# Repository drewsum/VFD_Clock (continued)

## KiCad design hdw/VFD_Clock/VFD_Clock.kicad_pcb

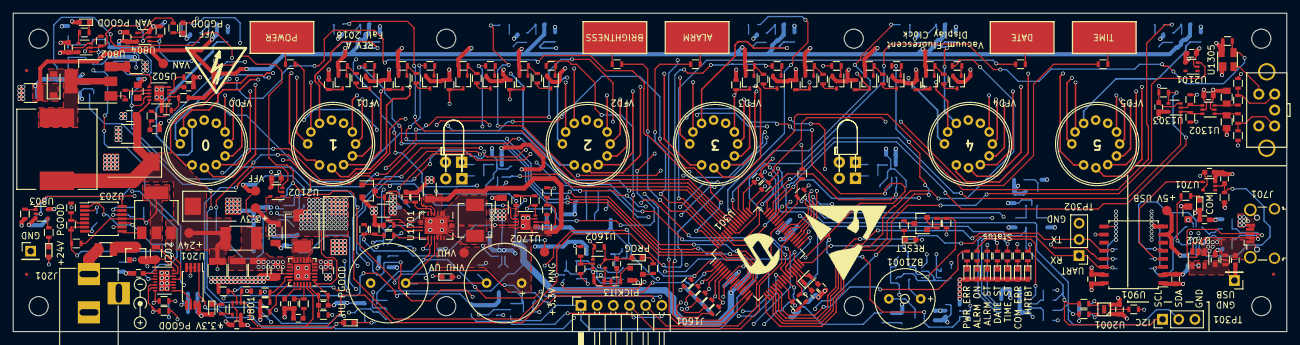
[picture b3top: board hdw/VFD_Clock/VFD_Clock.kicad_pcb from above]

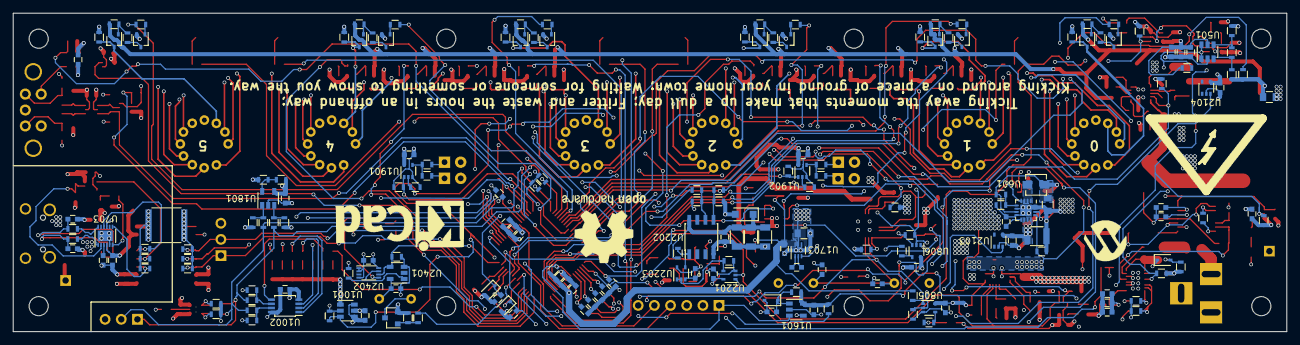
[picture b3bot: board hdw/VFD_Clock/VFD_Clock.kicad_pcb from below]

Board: 4 copper layers, 200.0 x 50.0 mm, 480 parts (186 on the bottom side), 265 nets.

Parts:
A201: 0x6F; Dummy_Empty
A301: MASTER; Dummy_Empty
A1001: 0x41; Dummy_Empty
A1801: 0x50/0x58(UID); Dummy_Empty
A2001: 0x44; Dummy_Empty
A2201: 0x6B; Dummy_Empty
BZ1001: AI-1027-TWT-3V-R
C201, C204, C302, C305, C502, C701, C703, C705, C706, C707, C801, C802, C803, C804, C805, C806, C901, C902, C1001, C1002, C1303, C1306, C1307, C1401, C1402, C1403, C1404, C1601, C1602, C1603, C1710, C1711, C1801, C1901, C1902, C2001, C2101, C2102, C2105, C2106, C2201, C2202, C2203, C2401, C2402: 0.1uF; C_0603
C202, C303, C306, C407, C503, C702, C710: 10nF; C_0603
C203, C304, C307, C504: 1nF; C_0603
C207: 2200pF; C_0603
C208, C404: 100pF; C_0603
C209, C510: 47uF; CP_Tantalum_Case-X_EIA-7343-43_Reflow
C308, C309: 9pF; C_0603
C401, C403, C405, C501, C602: 10uF; C_1210
C402: 5.1pF; C_0603
C406, C408: 1uF; C_0805
C409: 4.7pF; C_0603
C410: 100uF; C_1206
C411: 220uF; CP_Tantalum_Case-X_EIA-7343-43_Reflow
C505: 0.22uF; C_0603
C506: 6.8nF; C_0603
C507, C704: 4.7uF; C_0805
C508: 1uF; C_1210
C509, C511: 0.1uF; C_0805
C601: 150pF; C_0603
C603: 22uF; C_0805
C708, C709: 47pF; C_0603
C903: 22000pF; C_2220
C1304, C1305, C1707: 2.2uF; C_0805
C1701, C1702, C1706, C2204, C2205, C2206: 10uF; C_1206
C1703, C1704: 15F; SCCT30B156SRB
C1705: 470pF; C_0603
C1708: 1uF; C_0603
C1709: 4.7uF; C_0603
C2103, C2104, C2107, C2108: 330pF; C_0603
D501: SMD1200PL-TP‎; D_SOD-123
D702: Yellow; LED_0603
D801, D802, D803, D804, D805, D1007: Green; LED_0603
D806, D1003, D1008, D1009: Red; LED_0603
D1001, D1002: Orange; LED_0603
D1004, D1005, D1006: Blue; LED_0603
D1901, D1903: Green; LED_D3.0mm_Horizontal_O3.81mm_Z10.0mm
D1902, D1904: Green; LED_D3.0mm_Horizontal_O1.27mm_Z2.0mm
D2201: 1N5819; D_SOD-123F
F201: C1Q 2; Fuse_SMD1206_Reflow
FB401: 100; L_1812
FID2301, FID2302, FID2303: TP; Fiducial_0.5mm_Dia_1mm_Outer
J201: Power Input; BARREL_JACK
J701: USB_B_Micro; USB_Micro-B_Wuerth-629105150521_CircularHoles
J1601: Prog; PICKIT3_Header
L401: 0.82uH; L_Vishay_IHLP-2020
L501: 560uH; L_Wuerth_WE-PD-Typ-LS
L601: 2.2uH; L_Vishay_IHLP-1212
L701: 600R 0.5A; L_0603
L1701: 3.3uH; L_Vishay_IHLP-2020
MH2301, MH2302, MH2303, MH2304, MH2305, MH2306, MH2307, MH2308: 4-40 Mounting Hole; MountingHole_3mm
MK2301, MK2302, MK2303, MK2304, MK2305, MK2306, MK2307, MK2308: #4-40 Screw; Dummy_Empty
MK2309, MK2310, MK2311, MK2312, MK2313, MK2314, MK2315, MK2316: #4-40 Standoff; Dummy_Empty
Q201: Si2319CDS; SOT-23
Q202: PMT560ENEA; SOT-223
Q501: IRFL214TRPBF; SOT-223-3_TabPin2
Q1001, Q1002, Q1003, Q1701: 2N7002; SOT-23
Q1101, Q1102, Q1105, Q1106, Q1109, Q1110, Q1113, Q1114, Q1201, Q1202, Q1205, Q1206, Q1209, Q1210: PMSTA06; SOT-323_SC-70
Q1103, Q1104, Q1107, Q1108, Q1111, Q1112, Q1115, Q1116, Q1203, Q1204, Q1207, Q1208, Q1211, Q1212: BC856W; SOT-323_SC-70
R201, R203, R301, R302, R1012, R1013, R1604, R1708, R1801, R1805, R1806, R2004, R2005, R2204, R2205: 0; R_0603
R202, R204, R209, R210, R212, R303, R304, R305, R401, R405, R504, R506, R511, R601, R602, R701, R801, R802, R805, R806, R809, R810, R901, R902, R903, R904, R905, R906, R1003, R1005, R1014, R1015, R1101, R1102, R1109, R1110, R1117, R1118, R1125, R1126, R1201, R1202, R1209, R1210, R1217, R1218, R1303, R1308, R1309, R1312, R1313, R1314, R1402, R1404, R1406, R1601, R1602, R1603, R1605, R1802, R1803, R1804, R1901, R1902, R1907, R1908, R2001, R2002, R2003, R2201, R2202, R2203, R2206, R2401, R2402, R2403: 10k; R_0603
R205: 158k; R_0603
R206: 681; R_0603
R207: 3.74k; R_0603
R208, R704, R803, R804, R807, R808, R811, R812, R1004, R1006, R1007, R1008, R1009, R1010, R1011, R1016, R1018, R1310, R1311, R1408, R1903, R1904, R1905, R1906, R2101, R2102, R2103, R2104: 1k; R_0603
R211: 0.02; R_0805
R402: 49.9k; R_0603
R403: 18.2k; R_0603
R404, R1107, R1108, R1115, R1116, R1123, R1124, R1131, R1132, R1207, R1208, R1215, R1216, R1223, R1224, R1401, R1403, R1405, R1407: 100k; R_0603
R406, R1701, R1702, R1709, R1712, R1713: 1M; R_0603
R407: 412k; R_0603
R501: 196k; R_0603
R502: 237; R_0603
R503: 1.2k; R_0603
R505: 10.5k; R_0603
R507: 22k; R_0603
R508: 2; R_0603
R509: 0.51; R_1206
R510: 356k; R_0603
R603: 75k; R_0603
R604: 150k; R_0603
R702, R703: 27; R_0603
R1001, R1002, R1017: 10; R_0603
R1103, R1105, R1111, R1113, R1119, R1121, R1127, R1129, R1203, R1205, R1211, R1213, R1219, R1221: 220k; R_0603
R1104, R1106, R1112, R1114, R1120, R1122, R1128, R1130, R1204, R1206, R1212, R1214, R1220, R1222: 68k; R_0603
R1301, R1302, R1304, R1305, R1306: 220; R_0603
R1703: 124k; R_0603
R1704: 3.6k; R_0603
R1705: 2.2M; R_0603
R1706: 3.65k; R_0603
R1707: 340k; R_0603
R1710: 324k; R_0603
R1711: 276k; R_0603
SW1306: Select; ACZ11BR4E-15FA1-20C
TP201, TP702: TP; Pin_Header_Straight_1x01_Pitch2.54mm
TP203, TP401, TP501, TP601, TP701, TP1701, TP1702: TP; Measurement_Point_Round-SMD-Pad_Small
TP301: I2C; Pin_Header_Straight_1x03_Pitch2.54mm
TP302: USB_UART; Pin_Header_Straight_1x03_Pitch2.54mm
TP1301, TP1303: Date; SolderWirePad_single_SMD_5x10mm
TP1302: Time; SolderWirePad_single_SMD_5x10mm
TP1304: Alarm; SolderWirePad_single_SMD_5x10mm
TP1305: Brightness; SolderWirePad_single_SMD_5x10mm
U201: CDCS503; TSSOP-8_4.4x3mm_Pitch0.65mm
U202: LTC2946DE; DFN-16-1EP_3x4mm_Pitch0.45mm
U203: TPS2411PWR; TSSOP-14_4.4x5mm_Pitch0.65mm
U301: PIC18LF67K40-I_PT; TQFP-64_10x10mm_Pitch0.5mm
U401: LT8643S; QFN-24-1EP_4x4mm_Pitch0.5mm
U501: LT6700-1-S6; SOT-23-6
U502: LT3757; DFN-10-1EP_3x3mm_Pitch0.5mm
U601: TPS62150; QFN-16-1EP_3x3mm_Pitch0.5mm
U701: 74LVC1G17; SOT-353_SC-70-5
U702: TPD3S014DBVR; SOT-23-6
U703: FT234XD; DFN-12-1EP_3x3mm_Pitch0.45mm
U801, U802, U803, U804, U805, U1901, U1902, U2203: 74LVC1G38; SOT-353_SC-70-5
U806: 74LVC1G240; SOT-353_SC-70-5
U901: ISO7331C; SOIC-16W_7.5x10.3mm_Pitch1.27mm
U1001: TPS22929D; SOT-23-6
U1002: PCA9536DP; TSSOP-8_3x3mm_Pitch0.65mm
U1302: 74LVC2G14; SOT-363_SC-70-6
U1303: 74LVC1G79; SOT-353_SC-70-5
U1305: MAX6816; SOT-143
U1601: TL331; SOT-23-5
U1602: 74LVC1G86; SOT-353_SC-70-5
U1701: LTC3128-UFD; QFN-20-1EP_4x5mm_Pitch0.5mm
U1702: LTC4419DD; DFN-10-1EP_3x3mm_Pitch0.5mm
U1703: LTC3221; DFN-6-1EP_2x2mm_Pitch0.5mm
U1801: AT24CS01-STUM; SOT-23-5
U2001: OPT3001; USON-6_1EP_2mmx2mm_p0.65mm
U2101, U2102, U2103, U2104: MCP9700AT-HLT; SOT-353_SC-70-5
U2201: 74LVC1G08; SOT-353_SC-70-5
U2202: DS1683; SOIC-8_3.9x4.9mm_Pitch1.27mm
U2401: STWD100YNWWY3F; SOT-23-5
U2402: 74LVC2G74; VSSOP-8_2.3x2mm_Pitch0.5mm
VFD0, VFD1, VFD2, VFD3, VFD4, VFD5: IV-6
Y301: 32.768kHz; Crystal_SMD_2012-2pin_2.0x1.2mm
Z201: MMSZ5240BS; D_SOD-323
Z1402, Z1403: BZT52C3V3S; D_SOD-323
Z1601: BZT52C5V6S; D_SOD-323

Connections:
+3.3V_MNG: C302.1, C303.1, C304.1, C305.1, C306.1, C307.1, C1709.1, R305.2, R1701.2, R1712.2, R1713.2, TP1702.1, U301.10, U301.38, U1703.6
+3V3: BZ1001.1, C201.1, C202.1, C203.1, C409.1, C410.1, C411.1, C502.1, C503.1, C504.1, C602.1, C801.1, C802.1, C803.1, C804.1, C805.1, C806.1, C901.1, C1001.1, C1002.1, C1303.1, C1306.1, C1307.1, C1603.1, C1701.1, C1801.1, C1901.1, C1902.1, C2001.1, C2101.1, C2102.1, C2105.1, C2106.1, C2201.1, C2203.1, C2401.1, C2402.1, D801.2, D802.2, D803.2, D804.2, D805.2, D806.2, D1001.2, D1009.2, D1901.2, D1902.2, D1903.2, D1904.2, D2201.2, J1601.2, L401.2, R204.2, R209.2, R210.2, R303.2, R304.2, R401.2, R406.1, R504.2, R602.1, R1014.2, R1015.2, R1303.1, R1308.1, R1309.1, R1401.2, R1602.2, R1603.2, R1702.2, R1801.2, R1803.2, R1804.2, R2002.1, R2003.1, R2202.2, R2203.2, R2402.2, TP401.1, U201.7, U201.8, U401.1, U501.5, U601.10, U601.11, U601.12, U801.5, U802.5, U803.5, U804.5, U805.5, U806.5, U901.10, U901.16, U1001.4, U1001.6, U1002.8, U1302.5, U1303.5, U1305.4, U1602.5, U1701.7, U1801.4, U1901.5, U1902.5, U2001.1, U2101.4, U2102.4, U2103.4, U2104.4, U2201.5, U2203.5, U2401.5, U2402.8
+5V_USB: C701.1, C703.1, C704.1, C705.1, C902.1, D702.2, R701.1, TP701.1, U701.5, U702.4, U703.4, U703.9, U901.1, U901.7
+24V: C209.1, C401.1, C501.1, C510.1, C511.1, C1602.1, FB401.1, L501.1, Q202.3, R1405.2, R1601.2, TP203.1, U203.1, U203.10, U502.10, U1601.5
/USB/UART Converter/BRIDGE_USB+: R702.1, U703.12
/USB/UART Converter/BRIDGE_USB-: R703.2, U703.1
/USB/UART Converter/CONN_USB+: C708.1, J701.3, R702.2, U702.5
/USB/UART Converter/CONN_USB-: C709.1, J701.2, R703.1, U702.6
ACCUM: R212.2, U202.4, U301.36
Alarm_mTouch: R1305.2, U301.62
Ambient_Temp: C2103.1, R2101.1, U301.3
Anode_A: Q1103.3, R1107.1, VFD0.2, VFD1.2, VFD2.2, VFD3.2, VFD4.2, VFD5.2
Anode_B: Q1107.3, R1115.1, VFD0.1, VFD1.1, VFD2.1, VFD3.1, VFD4.1, VFD5.1
Anode_C: Q1111.3, R1123.1, VFD0.10, VFD1.10, VFD2.10, VFD3.10, VFD4.10, VFD5.10
Anode_D: Q1115.3, R1131.1, VFD0.6, VFD1.6, VFD2.6, VFD3.6, VFD4.6, VFD5.6
Anode_DP: Q1116.3, R1132.1, VFD0.11, VFD1.11, VFD2.11, VFD3.11, VFD4.11, VFD5.11
Anode_E: Q1104.3, R1108.1, VFD0.5, VFD1.5, VFD2.5, VFD3.5, VFD4.5, VFD5.5
Anode_F: Q1108.3, R1116.1, VFD0.4, VFD1.4, VFD2.4, VFD3.4, VFD4.4, VFD5.4
Anode_G: Q1112.3, R1124.1, VFD0.3, VFD1.3, VFD2.3, VFD3.3, VFD4.3, VFD5.3
Brightness_mTouch: R1306.2, U301.63
Buzzer: R1002.2, U301.25
Colon_1: R1901.1, U301.57, U1901.1
Colon_2: R1908.1, U301.56, U1902.1
DIM_PWM: R801.1, R802.1, R805.1, R806.1, R809.1, R810.1, R1003.1, R1902.1, R1907.1, U301.8, U801.2, U802.2, U803.2, U804.2, U805.2, U806.2, U1001.3, U1901.2, U1902.2
Date_mTouch: R1301.2, U301.61
Display_mTouch: R1304.2, U301.64
Encoder_DIR: R1314.1, U301.47, U1303.4
Encoder_STEP: R1312.1, U301.48, U1302.6, U1303.1
GND: C201.2, C202.2, C203.2, C204.2, C209.2, C302.2, C303.2, C304.2, C305.2, C306.2, C307.2, C308.2, C309.2, C401.2, C402.2, C403.2, C404.2, C405.2, C406.2, C407.2, C408.2, C410.2, C411.2, C501.2, C502.2, C503.2, C504.2, C505.2, C506.2, C507.2, C508.2, C509.2, C510.2, C511.2, C601.2, C602.2, C603.2, C801.2, C802.2, C803.2, C804.2, C805.2, C806.2, C901.2, C903.2, C1001.2, C1002.2, C1303.2, C1304.2, C1305.2, C1306.2, C1307.2, C1401.2, C1402.2, C1403.2, C1404.2, C1601.2, C1602.2, C1603.2, C1701.2, C1702.2, C1704.2, C1705.2, C1706.2, C1707.2, C1709.2, C1711.2, C1801.2, C1901.2, C1902.2, C2001.2, C2101.2, C2102.2, C2103.2, C2104.2, C2105.2, C2106.2, C2107.2, C2108.2, C2201.2, C2202.2, C2203.2, C2204.2, C2205.2, C2206.2, C2401.2, C2402.2, J201.2, J201.3, J1601.3, Q1001.2, Q1002.2, Q1003.2, Q1101.2, Q1102.2, Q1105.2, Q1106.2, Q1109.2, Q1110.2, Q1113.2, Q1114.2, Q1201.2, Q1202.2, Q1205.2, Q1206.2, Q1209.2, Q1210.2, Q1701.2, R202.1, R207.1, R208.1, R212.1, R403.2, R405.2, R407.2, R503.2, R505.2, R506.2, R509.2, R511.2, R601.2, R604.2, R801.2, R802.2, R805.2, R806.2, R809.2, R810.2, R901.1, R902.1, R903.1, R1003.2, R1005.1, R1107.2, R1108.2, R1115.2, R1116.2, R1123.2, R1124.2, R1131.2, R1132.2, R1207.2, R1208.2, R1215.2, R1216.2, R1223.2, R1224.2, R1312.2, R1313.2, R1314.2, R1402.1, R1404.1, R1406.1, R1408.1, R1604.1, R1605.1, R1703.1, R1704.1, R1707.1, R1711.1, R1802.1, R1901.2, R1902.2, R1907.2, R1908.2, R2001.2, R2201.1, R2401.1, R2403.1, SW1306.C, SW1306.S1, TP201.1, TP301.3, TP302.3, U201.2, U201.3, U201.4, U201.5, U202.11, U202.12, U202.14, U202.17, U203.7, U203.9, U301.9, U301.41, U401.3, U401.16, U401.25, U501.2, U502.5, U502.11, U601.6, U601.8, U601.15, U601.16, U601.17, U801.3, U802.3, U803.3, U804.3, U805.3, U806.3, U901.9, U901.15, U1001.2, U1001.5, U1002.4, U1302.2, U1303.3, U1305.1, U1601.2, U1602.3, U1701.21, U1702.4, U1702.11, U1703.4, U1703.7, U1801.2, U1901.3, U1902.3, U2001.3, U2101.2, U2102.2, U2103.2, U2104.2, U2201.3, U2202.4, U2203.3, U2401.3, U2402.1, U2402.2, U2402.4, VFD0.7, VFD1.7, VFD2.7, VFD3.7, VFD4.7, VFD5.7, Z1402.2, Z1403.2, Z1601.2
GND_USB: C701.2, C702.2, C703.2, C704.2, C705.2, C706.2, C707.2, C708.2, C709.2, C710.2, C902.2, C903.1, J701.5, R904.1, R905.1, R906.1, TP702.1, U701.3, U702.2, U703.5, U703.13, U901.2, U901.8
Grid_0: Q1203.3, R1207.1, VFD0.9
Grid_1: Q1207.3, R1215.1, VFD1.9
Grid_2: Q1211.3, R1223.1, VFD2.9
Grid_3: Q1204.3, R1208.1, VFD3.9
Grid_4: Q1208.3, R1216.1, VFD4.9
Grid_5: Q1212.3, R1224.1, VFD5.9
HOLDUP_ADC: R1708.1, U301.34
HOLDUP_PGOOD: R1701.1, U301.33, U805.1, U1701.12
ICSPCLK: J1601.5, U301.42
ICSPDAT: J1601.4, U301.37
ICSP_DETECT: R1001.2, R1605.2, U1602.4
IIC_SCL: R201.1, R301.1, R1013.1, R1805.1, R2005.2, R2204.1, TP301.1
IIC_SDA: R203.1, R302.1, R1012.1, R1806.1, R2004.1, R2205.1, TP301.2
MID: C1703.2, C1704.1, C1710.2, C1711.1, U1701.13
unnamed: BZ1001.2, Q1002.3
unnamed: C204.1, U202.2
unnamed: C207.1, C208.1, Q202.2, Q202.4, R205.2, R211.2, U202.15, U203.11
unnamed: C207.2, U203.13
unnamed: C208.2, U203.12
unnamed: C402.1, R402.1, U401.22
unnamed: C403.1, C405.1, C406.1, C408.1, FB401.2, R404.1, U401.5, U401.6, U401.13, U401.14
unnamed: C404.1, R402.2
unnamed: C407.1, U401.21
unnamed: C409.2, R406.2, R407.1, U401.24
unnamed: C505.1, U502.3
unnamed: C506.1, R507.2
unnamed: C507.1, U502.8
unnamed: C601.1, U601.9
unnamed: C702.1, R701.2, U701.2, U703.2
unnamed: C706.1, U703.3
unnamed: C707.1, L701.2, U702.1, U702.3
unnamed: C710.1, J701.1, L701.1
unnamed: C1304.1, R1310.2, U1302.1
unnamed: C1305.1, R1311.2, U1302.3
unnamed: C1601.1, R1601.1, U1601.1, Z1601.1
unnamed: C1702.1, R1709.2, U1701.2, U1701.3, U1702.1
unnamed: C1705.1, R1704.2, U1701.5
unnamed: C1706.1, C1707.1, U1702.8, U1703.3, U1703.5
unnamed: C1708.1, U1703.1
unnamed: C1708.2, U1703.2
unnamed: C2202.1, C2204.1, C2205.1, C2206.1, D2201.1, R2206.2, U2202.8
unnamed: D501.2, L501.2, Q501.2
unnamed: D702.1, R704.1
unnamed: D801.1, R803.1
unnamed: D802.1, R804.1
unnamed: D803.1, R807.1
unnamed: D804.1, R808.1
unnamed: D805.1, R811.1
unnamed: D806.1, R812.1
unnamed: D1001.1, R1004.2
unnamed: D1002.1, R1006.2
unnamed: D1003.1, R1007.2
unnamed: D1004.1, R1008.2
unnamed: D1005.1, R1009.2
unnamed: D1006.1, R1010.2
unnamed: D1007.1, R1011.2
unnamed: D1008.1, R1016.2
unnamed: D1009.1, R1018.2
unnamed: D1901.1, R1903.1
unnamed: D1902.1, R1904.1
unnamed: D1903.1, R1905.1
unnamed: D1904.1, R1906.1
unnamed: F201.1, Q201.3
unnamed: F201.2, J201.1
unnamed: L401.1, U401.8, U401.9, U401.10, U401.11, U401.12
unnamed: L601.1, U601.1, U601.2, U601.3
unnamed: L1701.1, U1701.1, U1701.19
unnamed: L1701.2, U1701.17, U1701.18
unnamed: Q201.1, R202.2, Z201.2
unnamed: Q201.2, R211.1, U202.1, U202.16, Z201.1
unnamed: Q202.1, U203.8
unnamed: Q501.1, R508.1
unnamed: Q501.3, R509.1, U502.6
unnamed: Q1001.1, R1001.1
unnamed: Q1001.3, R1004.1
unnamed: Q1002.1, R1002.1, R1005.2
unnamed: Q1003.1, R1017.1
unnamed: Q1003.3, R1018.1
unnamed: Q1101.1, R1101.2
unnamed: Q1101.3, R1104.2
unnamed: Q1102.1, R1102.2
unnamed: Q1102.3, R1106.2
unnamed: Q1103.1, R1103.2, R1104.1
unnamed: Q1104.1, R1105.2, R1106.1
unnamed: Q1105.1, R1109.2
unnamed: Q1105.3, R1112.2
unnamed: Q1106.1, R1110.2
unnamed: Q1106.3, R1114.2
unnamed: Q1107.1, R1111.2, R1112.1
unnamed: Q1108.1, R1113.2, R1114.1
unnamed: Q1109.1, R1117.2
unnamed: Q1109.3, R1120.2
unnamed: Q1110.1, R1118.2
unnamed: Q1110.3, R1122.2
unnamed: Q1111.1, R1119.2, R1120.1
unnamed: Q1112.1, R1121.2, R1122.1
unnamed: Q1113.1, R1125.2
unnamed: Q1113.3, R1128.2
unnamed: Q1114.1, R1126.2
unnamed: Q1114.3, R1130.2
unnamed: Q1115.1, R1127.2, R1128.1
unnamed: Q1116.1, R1129.2, R1130.1
unnamed: Q1201.1, R1201.2
unnamed: Q1201.3, R1204.2
unnamed: Q1202.1, R1202.2
unnamed: Q1202.3, R1206.2
unnamed: Q1203.1, R1203.2, R1204.1
unnamed: Q1204.1, R1205.2, R1206.1
unnamed: Q1205.1, R1209.2
unnamed: Q1205.3, R1212.2
unnamed: Q1206.1, R1210.2
unnamed: Q1206.3, R1214.2
unnamed: Q1207.1, R1211.2, R1212.1
unnamed: Q1208.1, R1213.2, R1214.1
unnamed: Q1209.1, R1217.2
unnamed: Q1209.3, R1220.2
unnamed: Q1210.1, R1218.2
unnamed: Q1210.3, R1222.2
unnamed: Q1211.1, R1219.2, R1220.1
unnamed: Q1212.1, R1221.2, R1222.1
unnamed: Q1701.1, U1702.7
unnamed: Q1701.3, R1702.1, U1701.4, U1701.9
unnamed: R201.2, R210.1, U202.8
unnamed: R203.2, R204.1, U202.6, U202.7
unnamed: R205.1, R206.2, U202.13, U203.6
unnamed: R206.1, R207.2, U203.5
unnamed: R208.2, U203.2
unnamed: R301.2, R304.1, U301.50
unnamed: R302.2, R303.1, U301.49
unnamed: R403.1, U401.18
unnamed: R404.2, R405.1, U401.17
unnamed: R501.2, R502.1, U501.3
unnamed: R502.2, R503.1, U501.4
unnamed: R505.1, U502.4
unnamed: R507.1, U502.1
unnamed: R508.2, U502.7
unnamed: R510.2, R511.1, U502.2
unnamed: R603.2, R604.1, U601.5
unnamed: R803.2, U801.4
unnamed: R804.2, U802.4
unnamed: R807.2, U803.4
unnamed: R808.2, U804.4
unnamed: R811.2, U805.4
unnamed: R812.2, U806.4
unnamed: R1012.2, R1015.1, U1002.7
unnamed: R1013.2, R1014.1, U1002.6
unnamed: R1301.1, TP1301.1
unnamed: R1302.1, TP1302.1
unnamed: R1304.1, TP1303.1
unnamed: R1305.1, TP1304.1
unnamed: R1306.1, TP1305.1
unnamed: R1308.2, R1310.1, SW1306.A
unnamed: R1309.2, R1311.1, SW1306.B
unnamed: R1313.1, U1302.4, U1303.2
unnamed: R1602.1, U1601.4, U1602.1
unnamed: R1603.1, R1604.2, U1602.2
unnamed: R1703.2, U1701.10
unnamed: R1705.1, R1706.2, U1701.11
unnamed: R1706.1, R1707.2, R1708.2, U1702.9
unnamed: R1709.1, R1710.2, U1702.3
unnamed: R1710.1, R1711.2, U1702.2
unnamed: R1801.1, R1802.2, U1801.5
unnamed: R1803.1, R1805.2, U1801.3
unnamed: R1804.1, R1806.2, U1801.1
unnamed: R1903.2, R1904.2, U1901.4
unnamed: R1905.2, R1906.2, U1902.4
unnamed: R2001.1, U2001.2
unnamed: R2002.2, R2004.2, U2001.6
unnamed: R2003.2, R2005.1, U2001.4
unnamed: R2101.2, U2101.3
unnamed: R2102.2, U2102.3
unnamed: R2103.2, U2103.3
unnamed: R2104.2, U2104.3
unnamed: R2201.2, U2201.4, U2203.1, U2203.2
unnamed: R2202.1, R2204.2, U2202.5
unnamed: R2203.1, R2205.2, U2202.6
unnamed: R2206.1, U2202.1, U2203.4
unnamed: R2402.1, U2401.1, U2402.7
unnamed: SW1306.S2, U1305.2
unnamed: U201.6, U202.9
POS3P3_ADC: C1401.1, R1401.1, R1402.2, U301.1
POS3P3_PGOOD: R401.1, U301.2, U401.23, U801.1
POS3P3_TEMP: C2107.1, R2103.1, U301.6
POS24_ADC: C1403.1, R1405.1, R1406.2, U301.23, Z1402.1
POS24_PGOOD: R209.1, U203.14, U301.24, U803.1
REF_CLK: U201.1, U301.31
Reset_Detect: R1017.2, R2403.2, U2402.5
Time_mTouch: R1302.2, U301.60
USB_DTR: R902.2, U301.46, U901.13
USB_DTR_ISO: R905.2, U701.4, U901.4
USB_UART_RX: R903.2, TP302.1, U301.20, U901.14
USB_UART_RX_ISO: R904.2, U703.7, U901.3
USB_UART_TX: R901.2, TP302.2, U301.19, U901.12
USB_UART_TX_ISO: R906.2, U703.10, U901.5
VAN: C508.1, C509.1, D501.1, Q1103.2, Q1104.2, Q1107.2, Q1108.2, Q1111.2, Q1112.2, Q1115.2, Q1116.2, Q1203.2, Q1204.2, Q1207.2, Q1208.2, Q1211.2, Q1212.2, R501.1, R510.1, R1103.1, R1105.1, R1111.1, R1113.1, R1119.1, R1121.1, R1127.1, R1129.1, R1203.1, R1205.1, R1211.1, R1213.1, R1219.1, R1221.1, R1407.2, TP501.1
VAN_ADC: C1404.1, R1407.1, R1408.2, U301.28, Z1403.1
VAN_PGOOD: R504.1, U301.27, U501.1, U501.6, U802.1, U2201.1
VAN_RUN: R506.1, U301.26, U502.9
VAN_Temp: C2108.1, R2104.1, U301.5
VD: D1002.2, D1003.2, D1004.2, D1005.2, D1006.2, D1007.2, D1008.2, U1001.1
VFF: C603.1, L601.2, R603.1, R1403.2, TP601.1, U601.7, U601.14, VFD0.8, VFD1.8, VFD2.8, VFD3.8, VFD4.8, VFD5.8
VFF_ADC: C1402.1, R1403.1, R1404.2, U301.43
VFF_PGOOD: R602.2, U301.44, U601.4, U804.1, U2201.2
VFF_RUN: R601.1, U301.45, U601.13
VFF_Temp: C2104.1, R2102.1, U301.4
VHU: C1703.1, C1710.1, R1705.2, TP1701.1, U1701.14, U1701.15, U1701.16, U1702.10
Watchdog_Poke: R2401.2, U301.32, U2401.4, U2402.6
drive_Anode_A: R1101.1, U301.18
drive_Anode_B: R1109.1, U301.17
drive_Anode_C: R1117.1, U301.16
drive_Anode_D: R1125.1, U301.15
drive_Anode_DP: R1126.1, U301.11
drive_Anode_E: R1102.1, U301.14
drive_Anode_F: R1110.1, U301.13
drive_Anode_G: R1118.1, U301.12
drive_Grid_0: R1201.1, U301.58
drive_Grid_1: R1209.1, U301.55
drive_Grid_2: R1217.1, U301.54
drive_Grid_3: R1202.1, U301.53
drive_Grid_4: R1210.1, U301.52
drive_Grid_5: R1218.1, U301.51
uC_SOSC+: C308.1, U301.29, Y301.1
uC_SOSC-: C309.1, U301.30, Y301.2
~Encoder_PB: R1303.2, U301.59, U1305.3
~HOLDUP_UV: R1713.1, U806.1, U1702.6
~MCLR: J1601.1, R305.1, U301.7, U1601.3
~POS3P3_UV: R1712.1, U301.35, U1702.5
~Status_Alarm_On: R1011.1, U1002.5
~Status_COM_Error: R1007.1, U301.40
~Status_Heartbeat: R1006.1, U301.39
~Status_Power_Error: R1016.1, U301.21
~Status_Set_Alarm: R1010.1, U1002.3
~Status_Set_Date: R1009.1, U1002.2
~Status_Set_Time: R1008.1, U1002.1
~USB_ACTIVE: R704.2, U703.6

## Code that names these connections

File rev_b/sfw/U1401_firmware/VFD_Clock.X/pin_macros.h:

#ifndef _PIN_MACROS_H    /* Guard against multiple inclusion */
#define _PIN_MACROS_H


#include <xc.h>

#define HIGH    1
#define LOW     0

// These pin macros allow for easier manipulation of GPIO with matching
// signal names from the hardware schematic

// Port A
#define ANODE_G_PIN             LATAbits.LATA0
#define POS1P2_VFF_RUN_PIN      LATAbits.LATA2
#define POS1P2_VFF_PGOOD_PIN    PORTAbits.RA3
#define POS12_PGOOD_PIN         PORTAbits.RA4
#define I2C_DSP_EN_PIN          LATAbits.LATA5
#define CAP_TOUCH_UP_PIN        PORTAbits.RA9
#define CAP_TOUCH_DOWN_PIN      PORTAbits.RA10

// Port B
#define CAP_TOUCH_RIGHT_PIN     PORTBbits.RB0
#define CAP_TOUCH_LEFT_PIN      PORTBbits.RB1
#define ANODE_A_PIN             LATBbits.LATB2
#define ANODE_B_PIN             LATBbits.LATB3
#define ANODE_C_PIN             LATBbits.LATB4
#define ANODE_D_PIN             LATBbits.LATB5
#define CAP_TOUCH_POWER_PIN     PORTBbits.RB8
#define nDISPLAY_DETECT_PIN     PORTBbits.RB9
#define CPU_EXCEPTION_LED_PIN   LATBbits.LATB10
#define ERROR_LED_PIN           LATBbits.LATB11

// Port C
#define COLON_0_PIN             LATCbits.LATC1
#define GRID_5_PIN              LATCbits.LATC2
#define GRID_4_PIN              LATCbits.LATC3
#define GRID_3_PIN              LATCbits.LATC4
#define POS60_VAN_PGOOD_PIN     PORTCbits.RC13
#define MCU_POSC_ENABLE_PIN     LATCbits.LATC15

// Port D
#define POS60_VAN_RUN_PIN       LATDbits.LATD0
#define I2C_EN_PIN              LATDbits.LATD9
#define POS3P3_PGOOD_PIN        PORTDbits.RD10
#define POS5_USB_PGOOD_PIN      PORTDbits.RD11
#define VBAT_PGOOD_PIN          PORTDbits.RD13

// Port E
#define nIO_LEVEL_SHIFT_ENABLE_PIN  LATEbits.LATE4
#define COLON_3_PIN             LATEbits.LATE5
#define COLON_2_PIN             LATEbits.LATE6
#define COLON_1_PIN             LATEbits.LATE7
#define ANODE_F_PIN             LATEbits.LATE8
#define ANODE_E_PIN             LATEbits.LATE9

// Port F
#define RESET_LED_PIN           LATFbits.LATF2
#define POS5_RUN_PIN            LATFbits.LATF4
#define POS5_PGOOD_PIN          PORTFbits.RF5
#define HEARTBEAT_LED_PIN       LATFbits.LATF12

// Port G
#define GRID_2_PIN              LATGbits.LATG6
#define GRID_1_PIN              LATGbits.LATG7
#define GRID_0_PIN              LATGbits.LATG8
#define ANODE_DP_PIN            LATGbits.LATG9
#define nBACKUP_RTC_CONFIG_PIN  PORTGbits.RG12
#define nTOF_CONFIG_PIN         PORTGbits.RG13
#define nTELEMETRY_CONFIG_PIN   PORTGbits.RG14
#define BUZZER_ENABLE_PIN       LATGbits.LATG15


#endif /* _PIN_MACROS_H */

/* *****************************************************************************
 End of File
 */

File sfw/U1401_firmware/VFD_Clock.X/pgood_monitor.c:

#include <stdio.h>

#include "pgood_monitor.h"

#include "pin_macros.h"

#include "terminal_control.h"

// this function prints current PGOOD status
void printPGOODStatus(void) {
 
    terminalTextAttributes(GREEN_COLOR, BLACK_COLOR, BOLD_FONT);
    printf("Current Power Supply Status:\r\n");
   
    if (POS12_PGOOD_PIN) terminalTextAttributes(GREEN_COLOR, BLACK_COLOR, NORMAL_FONT);
    else terminalTextAttributes(RED_COLOR, BLACK_COLOR, NORMAL_FONT);
    printf("    +12V Input Voltage is %s\n\r", POS12_PGOOD_PIN ? "within tolerance" : "out of tolerance");
    
    if (POS3P3_PGOOD_PIN) terminalTextAttributes(GREEN_COLOR, BLACK_COLOR, NORMAL_FONT);
    else terminalTextAttributes(RED_COLOR, BLACK_COLOR, NORMAL_FONT);
    printf("    +3.3V Power Supply is %s", POS12_PGOOD_PIN ? "enabled, " : "disabled\r\n");
    if (POS3P3_PGOOD_PIN) printf("output voltage is %s\r\n", POS3P3_PGOOD_PIN ? "within regulation" : "out of regulation");
    
    if (POS5_PGOOD_PIN) terminalTextAttributes(GREEN_COLOR, BLACK_COLOR, NORMAL_FONT);
    else terminalTextAttributes(RED_COLOR, BLACK_COLOR, NORMAL_FONT);
    printf("    +5V Power Supply is %s", POS5_RUN_PIN ? "enabled, " : "disabled\r\n");
    if (POS5_PGOOD_PIN) printf("output voltage is %s\r\n", POS5_PGOOD_PIN ? "within regulation" : "out of regulation");
    
    if (POS60_VAN_PGOOD_PIN) terminalTextAttributes(GREEN_COLOR, BLACK_COLOR, NORMAL_FONT);
    else terminalTextAttributes(RED_COLOR, BLACK_COLOR, NORMAL_FONT);
    printf("    +60VAN Power Supply is %s", POS60_VAN_RUN_PIN ? "enabled, " : "disabled\r\n");
    if (POS60_VAN_PGOOD_PIN) printf("output voltage is %s\r\n", POS60_VAN_PGOOD_PIN ? "within regulation" : "out of regulation");
    
    if (POS1P2_VFF_PGOOD_PIN) terminalTextAttributes(GREEN_COLOR, BLACK_COLOR, NORMAL_FONT);
    else terminalTextAttributes(RED_COLOR, BLACK_COLOR, NORMAL_FONT);
    printf("    +1.2VFF Power Supply is %s", POS1P2_VFF_RUN_PIN ? "enabled, " : "disabled\r\n");
    if (POS1P2_VFF_PGOOD_PIN) printf("output voltage is %s\r\n", POS1P2_VFF_PGOOD_PIN ? "within regulation" : "out of regulation");
    
    if (!nUSB_DETECT_PIN) terminalTextAttributes(GREEN_COLOR, BLACK_COLOR, NORMAL_FONT);
    else terminalTextAttributes(RED_COLOR, BLACK_COLOR, NORMAL_FONT);
    printf("    USB Bus Voltage is %s\n\r", !nUSB_DETECT_PIN ? "within tolerance" : "out of tolerance (or USB cable is unplugged)");
    
    if (VBAT_PGOOD_PIN) terminalTextAttributes(GREEN_COLOR, BLACK_COLOR, NORMAL_FONT);
    else terminalTextAttributes(RED_COLOR, BLACK_COLOR, NORMAL_FONT);
    printf("    Backup Battery is %s, battery is %s\n\r", 
            VBAT_ENABLE_PIN ? "in circuit" : "out of circuit",
            VBAT_PGOOD_PIN ? "charged" : "discharged");
    
    if (BCKP_ON_PIN) terminalTextAttributes(RED_COLOR, BLACK_COLOR, NORMAL_FONT);
    else terminalTextAttributes(GREEN_COLOR, BLACK_COLOR, NORMAL_FONT);
    printf("    Power Backup Circuit is %s\n\r", BCKP_ON_PIN ? "in circuit" : "out of circuit");
    
    terminalTextAttributesReset();
}

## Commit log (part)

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2018-07-04 Initial commit of KiCad schematic files/netlist/project for VFD Clock project
2018-07-14 Final commit of working copy for KiCad version 4.0.7, updating to KiCad 5
2018-07-14 Final final commit for KiCad version 4.0.7
2018-07-15 Revert "Final final commit for KiCad version 4.0.7"
    This reverts commit fbe75abb0d1613021aeb88c6dcc17fa8dcce395f.
2018-07-15 Initial commit of KiCad version 5 project
2018-07-15 Converted \root\ sheet to table of contents
2018-07-15 Added supercap backup circuits to backup supply sheet
2018-07-15 Resolved an issue with the field names of resistors on anode and grid driver sheets
2018-07-15 Populated tube life counter sheet
2018-07-15 Removed a ton of unused old files, not required for current project
2018-07-15 Updated UART USB converter sheet, and isolation sheet
2018-07-15 Removed unused USB Iso sheet
2018-07-17 Changed input current sensor to be upstream of ideal diode
2018-07-17 Moved SCL pin location on tube life timer
2018-07-17 Changed the status sheet drastically to use I/O expander, and changed PGOOD sheet to include HOLDUP_PGOOD LED
2018-07-17 Added HOLDUP voltage ADC monitoring
2018-07-17 Updated PDF to current changes
2018-07-17 Fixed an issue with input voltage rail to high side switch for status LEDs
2018-07-17 Added a ton of test points and more indicators for system state
2018-07-17 Updated PDF
2018-07-19 Added a config field for every part, DNP some I2C pullups, added I2C header, changed some serial port functionality
2018-07-19 Altered encoder circuit to use little logic to simplify firmware, resized active low signals to it on micro better, updated PDF
2018-07-19 Added mechanical sheet with moutning holes, hardware, graphical PCB symbols, and fiducials
2018-07-19 Added I2C Address symbols for I2C devices
2018-07-21 Changed +3.3V power supply to LTC3833 centered design
2018-07-21 Found component values for holdup circuits
2018-07-23 Annotated all components, finished assigning footprints, netlist generated
2018-07-23 Slight netlist modifications, pulled changes into PCB
2018-07-24 Changed POS3P3 MOSFETs, further schematic enhancements, footprint updates, and arranged a few more pages of components on PCB
2018-07-25 Switched to QFN micro, various footprint fixes, layed a a few more sheets out, changed puchbutton debouncers
2018-07-25 Arranged USB components, various footprint fixes, added GND_USB EMI cap
2018-07-25 Added a bunch of Digi-Key PN's
2018-07-28 Added input energy monitor
2018-07-28 Arranged VFF power supply components on PCB
2018-07-29 Removed LTC3833 for POS3P3 supply, replacing with LT8643S
2018-07-30 Finished POS3P3 redesign and cleaned other pages
2018-07-30 Arranged more components on PCB, cleaned up schematic, added page titles, finished finding DigiKey PN's
2018-07-31 Arranged components for backup power supply
2018-08-01 Arranged power input sheet on PCB (sinished arranging individual sheets), netlist cleanup)
2018-08-02 Placed mechanical components on PCB
2018-08-02 Moved fiducials
2018-08-02 Placed VFD tubes and colons
2018-08-02 moved VFD tubes further forward, placed power input circuit
2018-08-02 Placed grid driver circuits
2018-08-02 Placed USB and POS3P3 power supplies
2018-08-02 Placed backup supply and associated circuits
2018-08-02 Placed VAN supply and associated circuits
2018-08-02 Placed pushbuttons
2018-08-02 Started staging Micro and associated parts for placement
2018-08-05 Switched back to TQFP micro package, placed lots of aux circuits, grid drivers, anode drivers
2018-08-05 Finished first pass of arranging parts. Resized sheet to size A
2018-08-08 Started routing non-critical signals
2018-08-08 Routed more minor signals
2018-08-17 More power routing, random low priority signals
2018-08-18 More power routing
2018-08-18 More random power routing
2018-08-18 More random routing, started routing anode connections
2018-08-19 Finished routing anodes and grids
2018-08-19 Finished routing anode and grid control signals from micro, routed UART from micro
2018-08-19 Routed I2C and various analog signals
2018-08-19 More random analog routing, random small logic signals
2018-08-19 Routed more I2C and various analog/digital low voltage signals
2018-08-19 Routed almost all signals, pushbuttons remain
2018-08-19 Switched a few pushbutton pins to make layout easier
2018-08-21 Added render PNGs
2018-08-22 Added silkscreen symbols outlined in mechanical sheet, moved power connector
2018-08-23 Substantial Silkscreen Changes, rotated most ref des's, added symbols and text
2018-08-23 Added high frequency caps across holdup supercaps
2018-08-23 Added reset detection circuit
2018-08-23 Arranged and routed reset detect circuit on PCB
2018-09-05 Changed from mechanical pushbuttons to mTouch capacitive touch sensing
2019-04-09 Redesigned +1.2V VFF
2019-04-09 More revisions
2019-04-11 More work, project restructuring
2019-04-19 Added display board schematic, other additions to logic board
2019-04-19 Added +3.3V SW sheet
2019-12-23 Resurrected project
2019-12-24 Added USB telemetry, isolation, and POS60_VAN current sense
2019-12-28 Lots of schematic additions
2019-12-29 Started IV-6 display board, continued logic board development
2020-01-11 Added backup RTC, IO connector, other stuff
2020-01-11 Added readme
2020-01-18 Changed to configurable discrete gates, added VBAT stuff
2020-01-19 Display board tweaks, added buzzer, other stuff
2020-01-22 Reorganized logic board pages
2020-01-23 Assigned logic board I2C addresses
2020-01-24 Few hdw tweaks
2020-02-02 Added TOF to display board
2020-02-02 Added backup ADC circuits
2020-02-06 Few fixes, added BLE
2020-02-08 Finished arranging groups of parts
2020-02-09 placed most parts on board
2020-02-10 Started routing
2020-02-10 Lots more routing, primarily power stuff
2020-02-10 More routing
2020-02-11 Moar routing
2020-02-15 Changed buzzer clock, netlist changes
2020-02-15 Added two more colon signals, more low speed signal routes
2020-02-15 Finished first pass on routing
2020-02-15 Changed to taller samtec connector
2020-02-16 Added lots of info on silk, logos, etc
2020-02-24 Started display board PCB
2020-02-25 Added IV-1 colon tubes
2020-02-25 some display board routing, arrangment
2020-02-26 Routed grad and anode drive signals
2020-02-27 Finished display board layout first pass
2020-02-28 refactored a lot of display board stuff
2020-02-28 More display board fixes
2020-02-29 reclassed some nets, placed I2C devices
2020-03-01 Finished IV-6 layout, generated gerbers, BOM
2020-03-08 Adjusted BOM
2020-03-08 Added MCU firmware project
2020-03-11 git ignoring
2020-03-11 ignoring
2020-03-11 Added pin macros to firmware
2020-03-21 Ported heartbet timer
2020-03-21 Switched to POSC w/ PLL as clock source after boot
2020-03-21 Ported USB UART stuff
2020-03-21 fixed help message typo
2020-03-21 Ported prefetch, some USB commands
2020-03-21 Fixed some USB clock status issues
2020-03-21 Ported PMD setup
2020-03-21 error handler cleanup, more clock status fixes
2020-03-21 Added rail status, refactored some more serial commands
2020-03-21 Added rail control serial functions to enable/disable power supplies
2020-03-21 Ported RTCC stuff
2020-03-21 Added clock calibration python script
2020-03-26 Ported I2C control code
2020-03-27 More temp sensor I2C stuff
2020-03-28 Added RTCC status function, condensed peripheral status commands
2020-03-28 More help message cleanups
2020-03-28 Ported and gutted telemetry stuff
2020-03-28 Got I2C working again, no clock sticking
2020-03-28 more MCP9804 fix attempts
2020-03-29 Addded more power monitor stuff
2020-03-29 More telemetry enhancementS
2020-03-29 Added INA219 calibration setting function
2020-03-29 More INA219 additions
2020-03-29 More INA219 stuff
2020-03-29 Added live telemetry features
2020-03-29 Added MCP9804 stuff back in
2020-03-30 First pass on LTC4151 driver
2020-03-30 Fixed LTC4151 voltage measurement
2020-03-30 More LTC4151 fixes using TRBs for reading
2020-03-30 Refactored all I2C read stuff into TRBs for quicker bus response
2020-03-31 Added logic board time of flight query
2020-03-31 Added some DS3231 backup RTC stuff
2020-04-02 Trying to fix some stuff
2020-04-02 Few more bug fixes
2020-04-02 Reverted to before code breaking
2020-04-02 Added terminal window title control
2020-04-02 Went back to main call of usb_uart_lut, attempting to make behaviour more stable
2020-04-03 Added display board detection stuff
2020-04-03 Added display board time of flight stuff
2020-04-03 Added Timer status serial commands
2020-04-03 Added period and timer value prints to timer status function
2020-04-03 Added early framework for VFD multiplexing
2020-04-03 Added basic framework for driving grids and anodes
2020-04-04 Added more display control stuff
2020-04-04 Got all of VFD display working
2020-04-05 Added clock display control stuff
2020-04-05 Added updates for display board LEDs
2020-04-05 Added cap touch interrupt support
2020-04-06 Added some pushbutton handler functions
2020-04-11 Added WDT clearing in main()
2020-04-11 Added ability to set time through pushbuttons
2020-04-11 Added features to set date with pushbuttons
2020-04-11 Reworked menu flow to make it easier to use
2020-04-11 Streamlined menu selections
2020-04-11 More menu cleanups
2020-04-11 Fixed weekday display stuff, added ability to set with pushbuttons
2020-04-11 Changed 'set date' mode colon characters
2020-04-11 More lamp test improvements
2020-04-11 Added power toggle button functionality
2020-04-11 Removed 'set rail enable' serial command
2020-04-11 Added ability to set VFD brightness through pushbuttons
2020-04-11 Added display brightnes sserial command
2020-04-11 Added ability to set am/pm enable with pushbuttons
2020-04-11 Added serial command for setting time display format
2020-04-12 Added alarm variables and serial commands
2020-04-12 Added 'set alarm enable' menu, pushbutton control'
2020-04-12 Added alarm setting through pushbuttons
2020-04-12 Added alarm buzzer into clock
2020-04-12 Fixed IDN command response
2020-04-13 Fixed I2C addresses in schematic
2020-04-14 converted certain I2C variables to 32 bit types
2020-04-14 Removed error handler from cache
2020-04-14 Few I2C master driver optimizations
2020-04-14 Changed I2C Master ISR to IPL7
2020-04-14 Added automatic time recovery on reset
2020-04-14 fixed some help command strings
2020-04-15 Disable pushbutton IRQs when telemetry is enabled
2020-04-15 Adjusted some I2C transaction delays
2020-04-15 Removed more unused 10bit I2C bloat
2020-04-16 a few more i2c fix attempts
2020-04-18 Added some ADC code
2020-04-18 More ADC stuff
2020-04-18 Got ADC channels working correctly
2020-04-19 Added I2C master status serial message
2020-04-19 Added some I2C slave status commands
2020-04-19 Added more I2C slave status stuff
2020-04-19 Added LTC4151 status stuff
2020-04-19 Added temp sensor status messages
2020-04-19 Added DS1683 status messages
2020-04-19 Finished I2C slave status messages
2020-04-19 Added code for displaying more characters
2020-04-19 Changed alarm arm and 24hr setting from binary to true and false strings
2020-10-07 moved rev A data to rev_a directory
2020-10-08 started rev B schematic work
2020-10-09 Added USB UART level shifting, few PCB deletions
2020-10-09 PCB changes, deletions
2020-10-14 More sch work, ran ERC
2020-10-15 placed more new parts on board
2020-10-15 finished placing new parts
2020-10-17 More rev B PCB routing
2020-10-17 moar rev b rowting
2020-10-18 more routing on rev B pcb
2020-11-25 copied rev A firmware to start
2020-11-25 updated pin macros
2020-11-25 started updating pin setup
2020-11-25 Copied a lot of updated I2C device drivers, peripheral drivers
2020-11-25 more I2C port fixes
2020-11-27 fixed a lot of legacy I2C drivers
2020-11-27 overhauled telemetry variables
2020-11-27 fixed some PGOOD monitor stuff
2020-11-27 made a lot of functionality hardstrap configurable
2020-12-14 lots of bug fixes, got rev b firmware started
2020-12-15 fixed power button INT mapping
2020-12-15 fixed PORT IOC interrupt bug
2020-12-15 more debugging
2020-12-15 added set power serial command
2020-12-16 added serial command for setting display board
2020-12-16 added lots of string fixes, firmware and hardware revision string macros
2020-12-16 added FTDI flash image, more str improvements, changed to boot with display off
2020-12-23 added rev b script
2021-01-09 pushbutton/backup RTC bugfix
